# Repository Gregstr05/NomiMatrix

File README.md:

# NomiMatrix
Custom WS2812b LED matrix

## TODO:
- Create software prototype for the controller
- design a pcb for the controller

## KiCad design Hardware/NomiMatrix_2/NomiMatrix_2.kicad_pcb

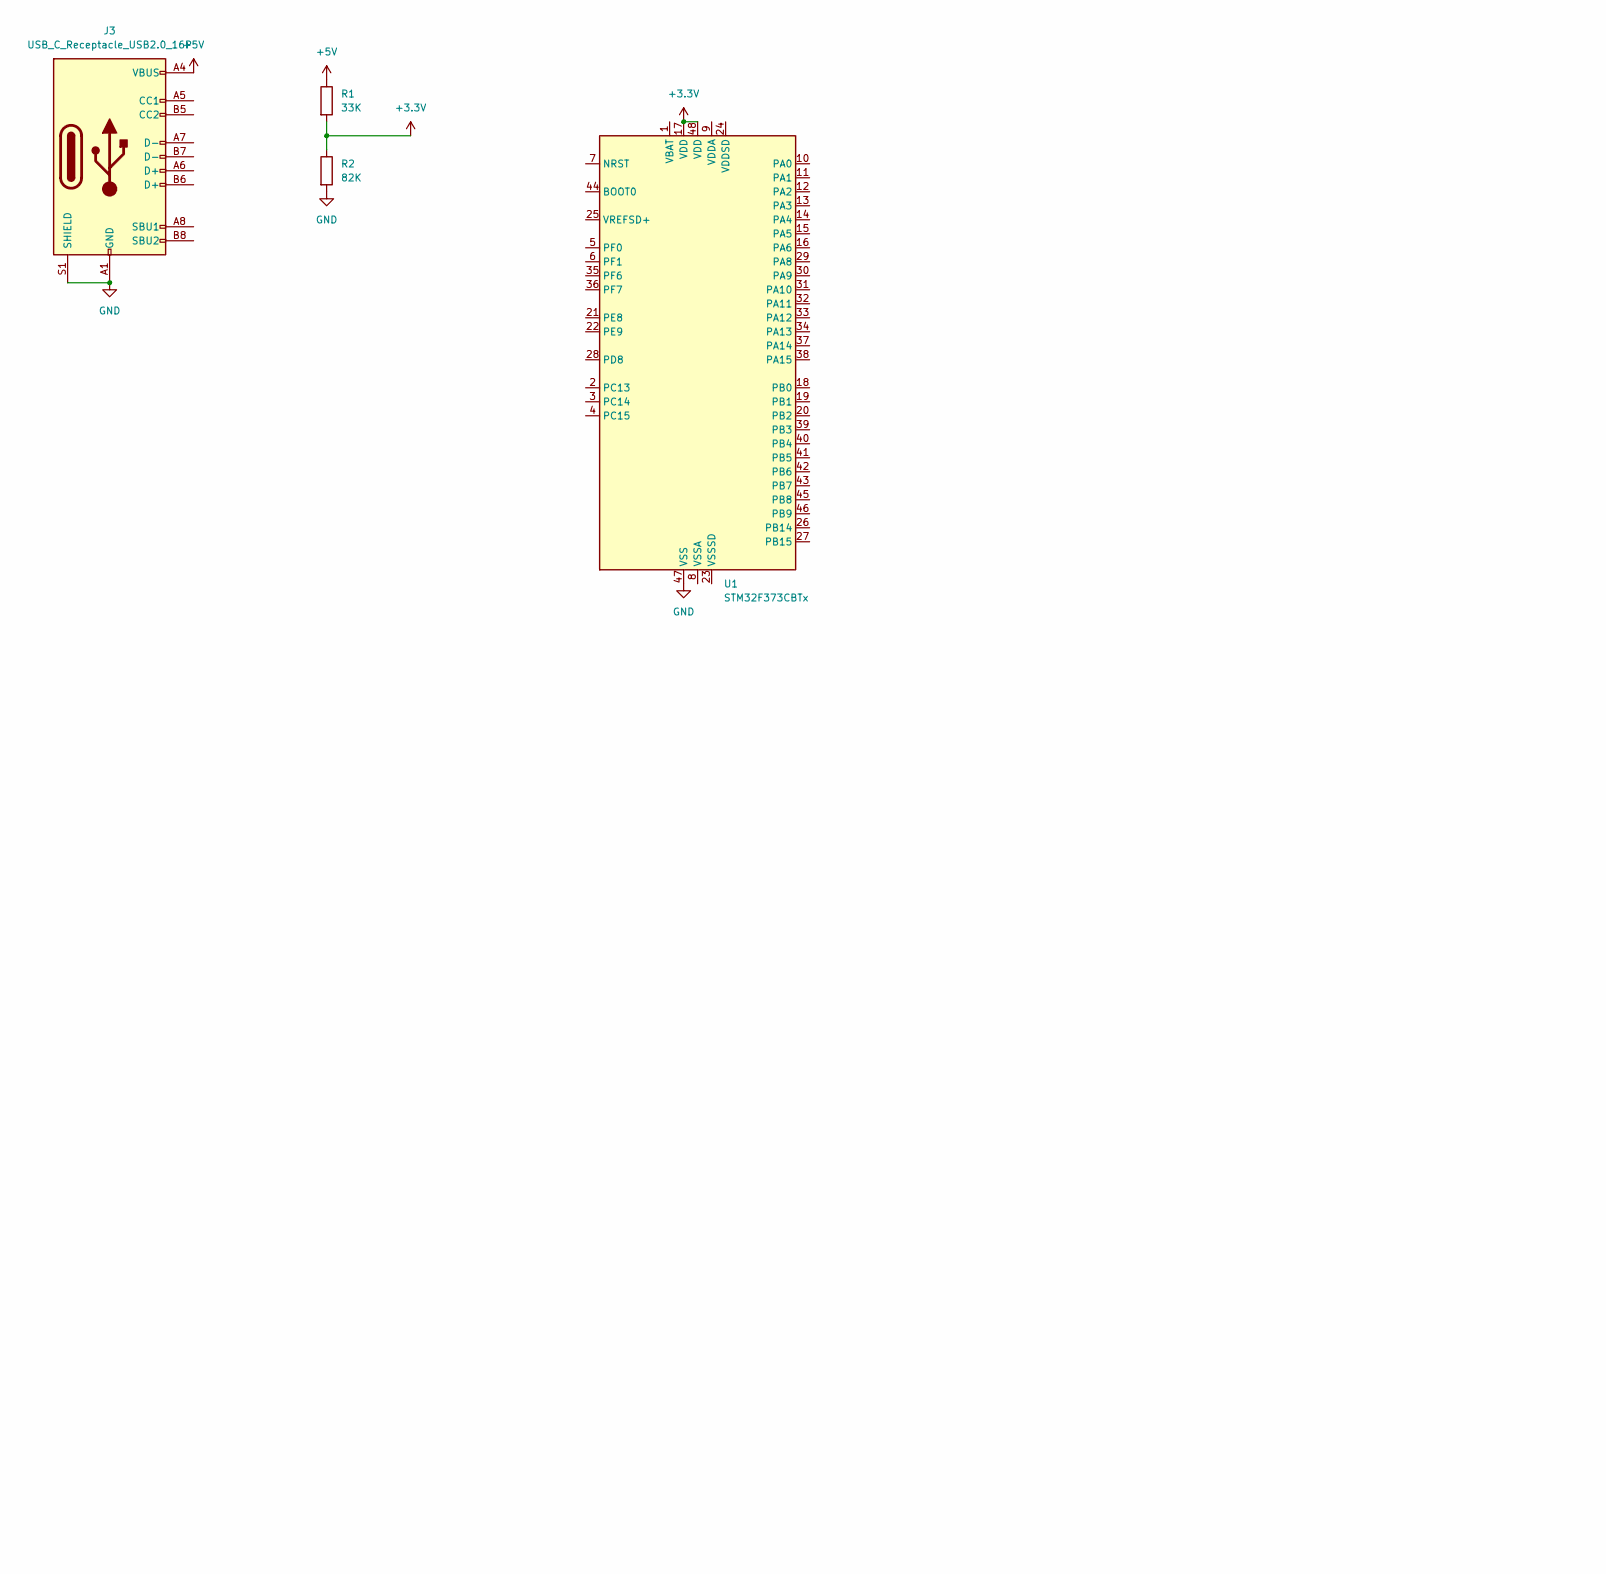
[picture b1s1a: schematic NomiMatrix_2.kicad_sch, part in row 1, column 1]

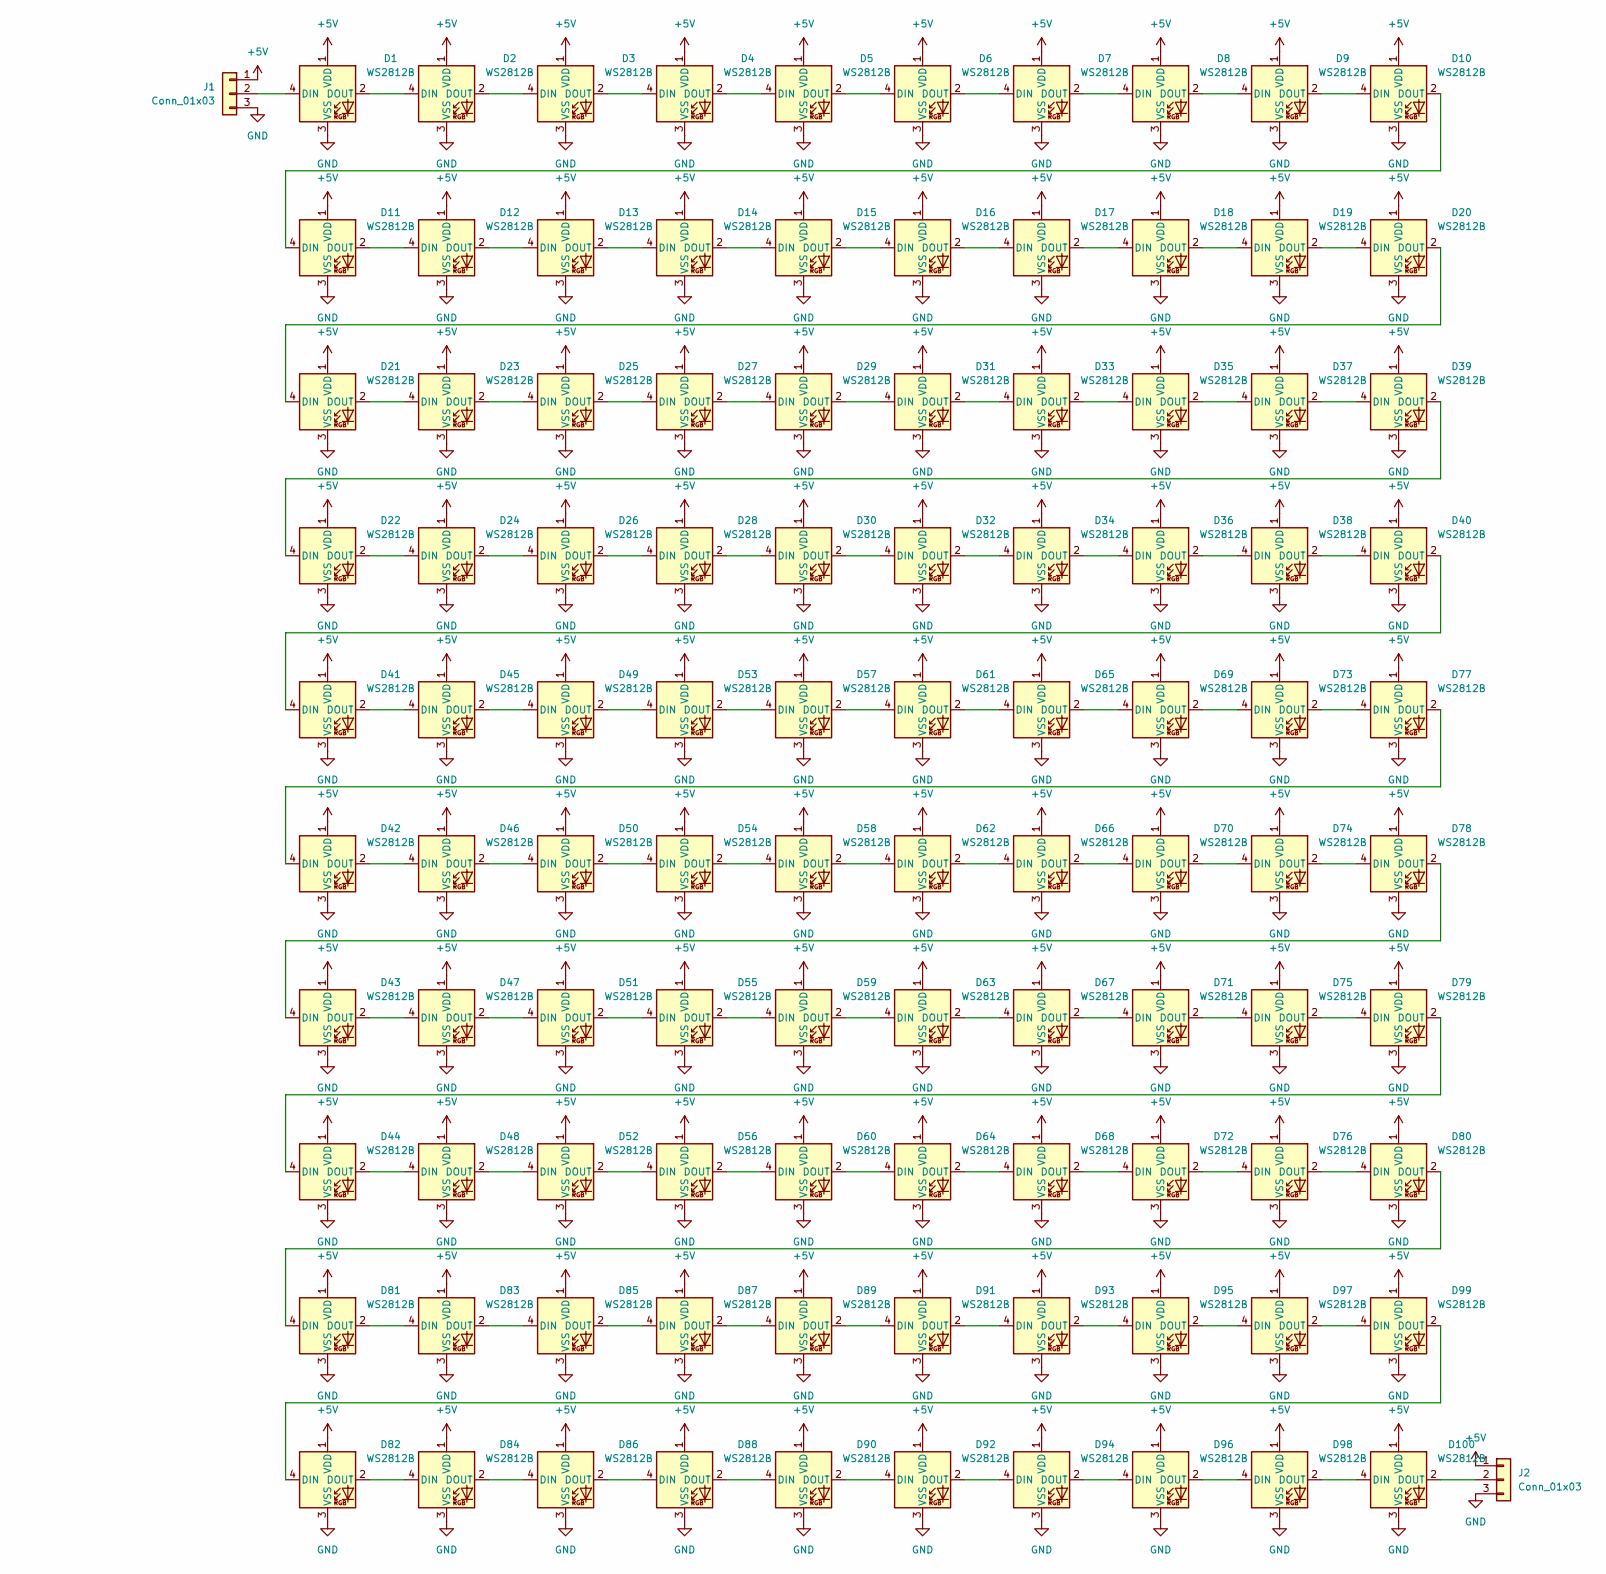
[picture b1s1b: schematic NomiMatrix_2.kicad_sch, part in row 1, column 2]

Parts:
D1, D2, D3, D4, D5, D6, D7, D8, D9, D10, D11, D12, D13, D14, D15, D16, D17, D18, D19, D20, D21, D22, D23, D24, D25, D26, D27, D28, D29, D30, D31, D32, D33, D34, D35, D36, D37, D38, D39, D40, D41, D42, D43, D44, D45, D46, D47, D48, D49, D50, D51, D52, D53, D54, D55, D56, D57, D58, D59, D60, D61, D62, D63, D64, D65, D66, D67, D68, D69, D70, D71, D72, D73, D74, D75, D76, D77, D78, D79, D80, D81, D82, D83, D84, D85, D86, D87, D88, D89, D90, D91, D92, D93, D94, D95, D96, D97, D98, D99, D100: WS2812B; LED_WS2812B_PLCC4_5.0x5.0mm_P3.2mm
J1, J2: Conn_01x03
J3: USB_C_Receptacle_USB2.0_16P
R1: 33K
R2: 82K
U1: STM32F373CBTx; LQFP-48_7x7mm_P0.5mm

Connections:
+3.3V: R1.2, R2.1, U1.17 (VDD), U1.48 (VDD)
+5V: D1.1 (VDD), D2.1 (VDD), D3.1 (VDD), D4.1 (VDD), D5.1 (VDD), D6.1 (VDD), D7.1 (VDD), D8.1 (VDD), D9.1 (VDD), D10.1 (VDD), D11.1 (VDD), D12.1 (VDD), D13.1 (VDD), D14.1 (VDD), D15.1 (VDD), D16.1 (VDD), D17.1 (VDD), D18.1 (VDD), D19.1 (VDD), D20.1 (VDD), D21.1 (VDD), D22.1 (VDD), D23.1 (VDD), D24.1 (VDD), D25.1 (VDD), D26.1 (VDD), D27.1 (VDD), D28.1 (VDD), D29.1 (VDD), D30.1 (VDD), D31.1 (VDD), D32.1 (VDD), D33.1 (VDD), D34.1 (VDD), D35.1 (VDD), D36.1 (VDD), D37.1 (VDD), D38.1 (VDD), D39.1 (VDD), D40.1 (VDD), D41.1 (VDD), D42.1 (VDD), D43.1 (VDD), D44.1 (VDD), D45.1 (VDD), D46.1 (VDD), D47.1 (VDD), D48.1 (VDD), D49.1 (VDD), D50.1 (VDD), D51.1 (VDD), D52.1 (VDD), D53.1 (VDD), D54.1 (VDD), D55.1 (VDD), D56.1 (VDD), D57.1 (VDD), D58.1 (VDD), D59.1 (VDD), D60.1 (VDD), D61.1 (VDD), D62.1 (VDD), D63.1 (VDD), D64.1 (VDD), D65.1 (VDD), D66.1 (VDD), D67.1 (VDD), D68.1 (VDD), D69.1 (VDD), D70.1 (VDD), D71.1 (VDD), D72.1 (VDD), D73.1 (VDD), D74.1 (VDD), D75.1 (VDD), D76.1 (VDD), D77.1 (VDD), D78.1 (VDD), D79.1 (VDD), D80.1 (VDD), D81.1 (VDD), D82.1 (VDD), D83.1 (VDD), D84.1 (VDD), D85.1 (VDD), D86.1 (VDD), D87.1 (VDD), D88.1 (VDD), D89.1 (VDD), D90.1 (VDD), D91.1 (VDD), D92.1 (VDD), D93.1 (VDD), D94.1 (VDD), D95.1 (VDD), D96.1 (VDD), D97.1 (VDD), D98.1 (VDD), D99.1 (VDD), D100.1 (VDD), J1.1, J2.1, J3.A4 (VBUS), J3.A9 (VBUS), J3.B4 (VBUS), J3.B9 (VBUS), R1.1
GND: D1.3 (VSS), D2.3 (VSS), D3.3 (VSS), D4.3 (VSS), D5.3 (VSS), D6.3 (VSS), D7.3 (VSS), D8.3 (VSS), D9.3 (VSS), D10.3 (VSS), D11.3 (VSS), D12.3 (VSS), D13.3 (VSS), D14.3 (VSS), D15.3 (VSS), D16.3 (VSS), D17.3 (VSS), D18.3 (VSS), D19.3 (VSS), D20.3 (VSS), D21.3 (VSS), D22.3 (VSS), D23.3 (VSS), D24.3 (VSS), D25.3 (VSS), D26.3 (VSS), D27.3 (VSS), D28.3 (VSS), D29.3 (VSS), D30.3 (VSS), D31.3 (VSS), D32.3 (VSS), D33.3 (VSS), D34.3 (VSS), D35.3 (VSS), D36.3 (VSS), D37.3 (VSS), D38.3 (VSS), D39.3 (VSS), D40.3 (VSS), D41.3 (VSS), D42.3 (VSS), D43.3 (VSS), D44.3 (VSS), D45.3 (VSS), D46.3 (VSS), D47.3 (VSS), D48.3 (VSS), D49.3 (VSS), D50.3 (VSS), D51.3 (VSS), D52.3 (VSS), D53.3 (VSS), D54.3 (VSS), D55.3 (VSS), D56.3 (VSS), D57.3 (VSS), D58.3 (VSS), D59.3 (VSS), D60.3 (VSS), D61.3 (VSS), D62.3 (VSS), D63.3 (VSS), D64.3 (VSS), D65.3 (VSS), D66.3 (VSS), D67.3 (VSS), D68.3 (VSS), D69.3 (VSS), D70.3 (VSS), D71.3 (VSS), D72.3 (VSS), D73.3 (VSS), D74.3 (VSS), D75.3 (VSS), D76.3 (VSS), D77.3 (VSS), D78.3 (VSS), D79.3 (VSS), D80.3 (VSS), D81.3 (VSS), D82.3 (VSS), D83.3 (VSS), D84.3 (VSS), D85.3 (VSS), D86.3 (VSS), D87.3 (VSS), D88.3 (VSS), D89.3 (VSS), D90.3 (VSS), D91.3 (VSS), D92.3 (VSS), D93.3 (VSS), D94.3 (VSS), D95.3 (VSS), D96.3 (VSS), D97.3 (VSS), D98.3 (VSS), D99.3 (VSS), D100.3 (VSS), J1.3, J2.3, J3.A1 (GND), J3.A12 (GND), J3.B1 (GND), J3.B12 (GND), J3.S1 (SHIELD), R2.2, U1.47 (VSS)
unnamed: D1.4 (DIN), J1.2
unnamed: D1.2 (DOUT), D2.4 (DIN)
unnamed: D2.2 (DOUT), D3.4 (DIN)
unnamed: D3.2 (DOUT), D4.4 (DIN)
unnamed: D4.2 (DOUT), D5.4 (DIN)
unnamed: D5.2 (DOUT), D6.4 (DIN)
unnamed: D6.2 (DOUT), D7.4 (DIN)
unnamed: D7.2 (DOUT), D8.4 (DIN)
unnamed: D8.2 (DOUT), D9.4 (DIN)
unnamed: D9.2 (DOUT), D10.4 (DIN)
unnamed: D10.2 (DOUT), D11.4 (DIN)
unnamed: D11.2 (DOUT), D12.4 (DIN)
unnamed: D12.2 (DOUT), D13.4 (DIN)
unnamed: D13.2 (DOUT), D14.4 (DIN)
unnamed: D14.2 (DOUT), D15.4 (DIN)
unnamed: D15.2 (DOUT), D16.4 (DIN)
unnamed: D16.2 (DOUT), D17.4 (DIN)
unnamed: D17.2 (DOUT), D18.4 (DIN)
unnamed: D18.2 (DOUT), D19.4 (DIN)
unnamed: D19.2 (DOUT), D20.4 (DIN)
unnamed: D20.2 (DOUT), D21.4 (DIN)
unnamed: D21.2 (DOUT), D23.4 (DIN)
unnamed: D22.4 (DIN), D39.2 (DOUT)
unnamed: D22.2 (DOUT), D24.4 (DIN)
unnamed: D23.2 (DOUT), D25.4 (DIN)
unnamed: D24.2 (DOUT), D26.4 (DIN)
unnamed: D25.2 (DOUT), D27.4 (DIN)
unnamed: D26.2 (DOUT), D28.4 (DIN)
unnamed: D27.2 (DOUT), D29.4 (DIN)
unnamed: D28.2 (DOUT), D30.4 (DIN)
unnamed: D29.2 (DOUT), D31.4 (DIN)
unnamed: D30.2 (DOUT), D32.4 (DIN)
unnamed: D31.2 (DOUT), D33.4 (DIN)
unnamed: D32.2 (DOUT), D34.4 (DIN)
unnamed: D33.2 (DOUT), D35.4 (DIN)
unnamed: D34.2 (DOUT), D36.4 (DIN)
unnamed: D35.2 (DOUT), D37.4 (DIN)
unnamed: D36.2 (DOUT), D38.4 (DIN)
unnamed: D37.2 (DOUT), D39.4 (DIN)
unnamed: D38.2 (DOUT), D40.4 (DIN)
unnamed: D40.2 (DOUT), D41.4 (DIN)
unnamed: D41.2 (DOUT), D45.4 (DIN)
unnamed: D42.4 (DIN), D77.2 (DOUT)
unnamed: D42.2 (DOUT), D46.4 (DIN)
unnamed: D43.4 (DIN), D78.2 (DOUT)
unnamed: D43.2 (DOUT), D47.4 (DIN)
unnamed: D44.4 (DIN), D79.2 (DOUT)
unnamed: D44.2 (DOUT), D48.4 (DIN)
unnamed: D45.2 (DOUT), D49.4 (DIN)
unnamed: D46.2 (DOUT), D50.4 (DIN)
unnamed: D47.2 (DOUT), D51.4 (DIN)
unnamed: D48.2 (DOUT), D52.4 (DIN)
unnamed: D49.2 (DOUT), D53.4 (DIN)
unnamed: D50.2 (DOUT), D54.4 (DIN)
unnamed: D51.2 (DOUT), D55.4 (DIN)
unnamed: D52.2 (DOUT), D56.4 (DIN)
unnamed: D53.2 (DOUT), D57.4 (DIN)
unnamed: D54.2 (DOUT), D58.4 (DIN)
unnamed: D55.2 (DOUT), D59.4 (DIN)
unnamed: D56.2 (DOUT), D60.4 (DIN)
unnamed: D57.2 (DOUT), D61.4 (DIN)
unnamed: D58.2 (DOUT), D62.4 (DIN)
unnamed: D59.2 (DOUT), D63.4 (DIN)
unnamed: D60.2 (DOUT), D64.4 (DIN)
unnamed: D61.2 (DOUT), D65.4 (DIN)
unnamed: D62.2 (DOUT), D66.4 (DIN)
unnamed: D63.2 (DOUT), D67.4 (DIN)
unnamed: D64.2 (DOUT), D68.4 (DIN)
unnamed: D65.2 (DOUT), D69.4 (DIN)
unnamed: D66.2 (DOUT), D70.4 (DIN)
unnamed: D67.2 (DOUT), D71.4 (DIN)
unnamed: D68.2 (DOUT), D72.4 (DIN)
unnamed: D69.2 (DOUT), D73.4 (DIN)
unnamed: D70.2 (DOUT), D74.4 (DIN)
unnamed: D71.2 (DOUT), D75.4 (DIN)
unnamed: D72.2 (DOUT), D76.4 (DIN)
unnamed: D73.2 (DOUT), D77.4 (DIN)
unnamed: D74.2 (DOUT), D78.4 (DIN)
unnamed: D75.2 (DOUT), D79.4 (DIN)
unnamed: D76.2 (DOUT), D80.4 (DIN)
unnamed: D80.2 (DOUT), D81.4 (DIN)
unnamed: D81.2 (DOUT), D83.4 (DIN)
unnamed: D82.4 (DIN), D99.2 (DOUT)
unnamed: D82.2 (DOUT), D84.4 (DIN)
unnamed: D83.2 (DOUT), D85.4 (DIN)
unnamed: D84.2 (DOUT), D86.4 (DIN)
unnamed: D85.2 (DOUT), D87.4 (DIN)
unnamed: D86.2 (DOUT), D88.4 (DIN)
unnamed: D87.2 (DOUT), D89.4 (DIN)
unnamed: D88.2 (DOUT), D90.4 (DIN)
unnamed: D89.2 (DOUT), D91.4 (DIN)
unnamed: D90.2 (DOUT), D92.4 (DIN)
unnamed: D91.2 (DOUT), D93.4 (DIN)
unnamed: D92.2 (DOUT), D94.4 (DIN)
unnamed: D93.2 (DOUT), D95.4 (DIN)
unnamed: D94.2 (DOUT), D96.4 (DIN)
unnamed: D95.2 (DOUT), D97.4 (DIN)
unnamed: D96.2 (DOUT), D98.4 (DIN)
unnamed: D97.2 (DOUT), D99.4 (DIN)
unnamed: D98.2 (DOUT), D100.4 (DIN)
unnamed: D100.2 (DOUT), J2.2

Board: 2 copper layers, 101 parts (0 on the bottom side), 102 nets, no tracks yet.

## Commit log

2024-06-25 Added the already done and manufactured boards to this repository
2024-06-25 Added gitignore
2024-06-25 Setup for controlling WS2812b LEDs with STM32 nucleo board and show a rainbow pattern with oscilating brightness
2024-06-28 Added scrolling to the rainbow
2024-06-28 Updated device configuration for SD card support
2024-06-28 Updated driver for the right configuration and SPI
    Also finally ignored the .metadata folder
2024-06-28 Added temporary reading a hard coded file from SD card for testing
    This will be removed and implemented a simple "scripting" method for giving data to the matrix without a dedicated controller
2025-11-24 Created a KiCad project for Nomi Matrix redesign with an integrated controller and fixed issues with the PCB
2025-11-24 recreated basic matrix
2025-11-25 Added an USB and the microcontroller chip, that will be used (becuase I have a lot of them)
2025-11-25 Started working on a PCB layout, but that will take a long time, will finish later.
